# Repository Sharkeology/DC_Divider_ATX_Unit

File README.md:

# DC Divider Project - ATX Base Unit

The ATX Base Unit is part of the larger DC Divider project meant for powering various 12, 9 and 5 volt powered devices (namely games consoles and A/V equipment) from a single ATX power supply unit. The Base Unit was made with the intention of being simple to assemble by beginners and uses off-the-shelf parts and modules.

## Bill of Materials

- 1 x ATX Base Unit PCB
- 1 x Right Angle ATX connector (Molex MiniFit Jr) - PRT-09498
- 3 x MINIVAL-style fuse holders (KEYS3568)
- 1 x LM2596 Adjustable Buck Converter Module
- 3 x Phoenix MSTB-style 2-pin connectors (5.08mm pin spacing)

Once assembled and connected to an ATX supply, the LM2596 module's output voltage can be adjusted to the users needs (although the project was made with 9 volts in mind).

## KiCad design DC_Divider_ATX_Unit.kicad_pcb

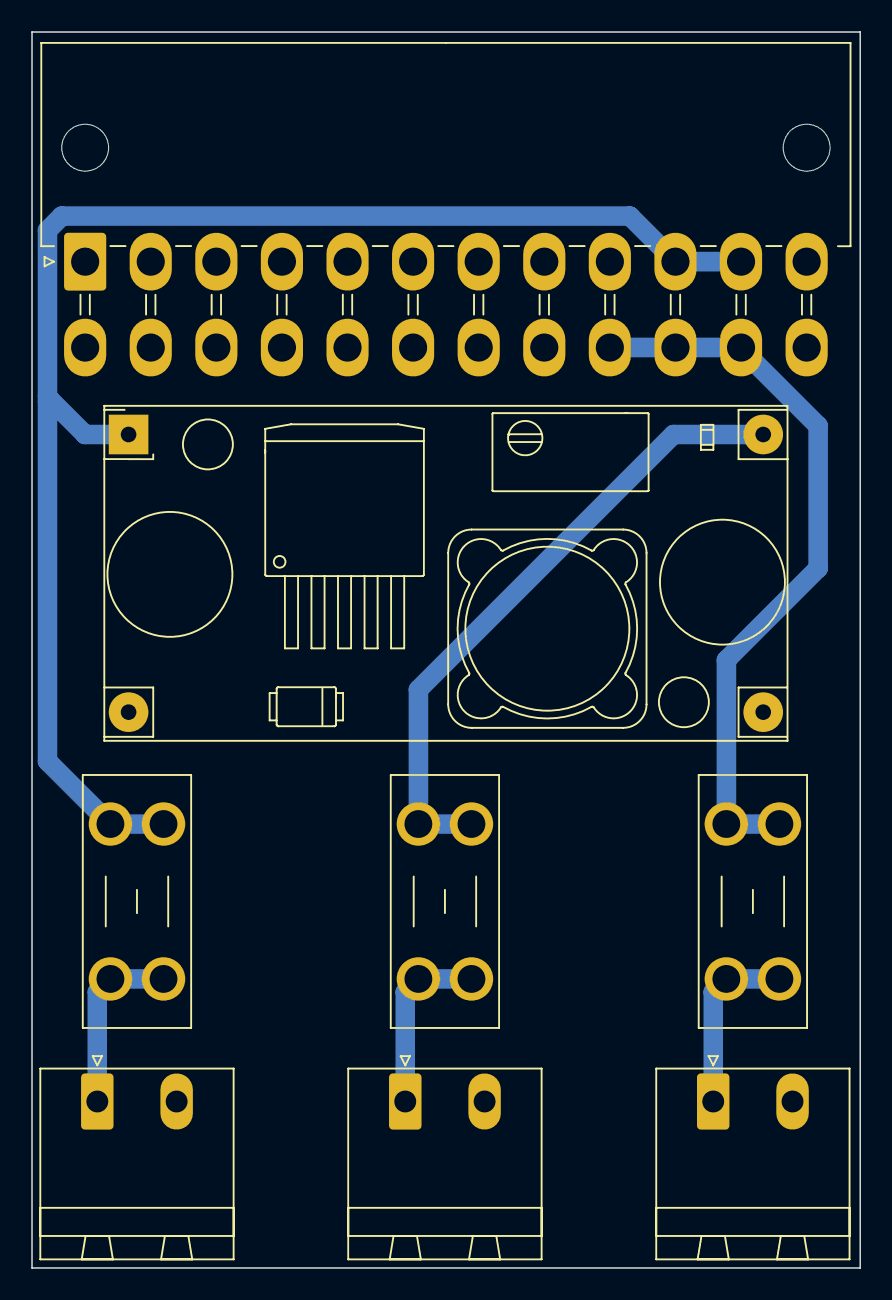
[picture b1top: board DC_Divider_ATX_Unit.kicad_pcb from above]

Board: 2 copper layers, 53.0 x 79.1 mm, 8 parts (0 on the bottom side), 7 nets.

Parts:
F1, F2, F3: Fuse; Fuseholder_Blade_Mini_Keystone_3568
J1: ATX-24; Molex_Mini-Fit_Jr_5569-24A2_2x12_P4.20mm_Horizontal
J2, J3, J4: Conn_01x02; PhoenixContact_MSTBA_2,5_2-G-5,08_1x02_P5.08mm_Horizontal
U1: YAAJ_DCDC_StepDown_LM2596

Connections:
+5V: F3.1, J1.4 (+5V), J1.6 (+5V), J1.21 (+5V), J1.22 (+5V), J1.23 (+5V)
+9V: F2.1, U1.4 (Vout)
+12V: F1.1, J1.10 (+12V), J1.11 (+12V), U1.1 (Vin)
GND: J1.3 (GND), J1.5 (GND), J1.7 (GND), J1.15 (GND), J1.16 (PS_ON#), J1.17 (GND), J1.18 (GND), J1.19 (GND), J1.24 (GND), J2.2, J3.2, J4.2, U1.2 (GND), U1.3 (GND)
unnamed: F1.2, J2.1
unnamed: F2.2, J3.1
unnamed: F3.2, J4.1

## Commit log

2023-06-14 Update README.md
    Included information in README
2023-06-14 Create LICENSE
2023-06-14 Uploaded repo contents.
2023-07-04 Revised PCB design w/ space for fuse holders.
    Minival-like blade fuse holders were included in series with each power rail in order to prevent catastrophic damage to the board in a short circuit/overcurrent situation.
2023-07-04 Update README.md
    Revised BOM and KiCad render.
2023-07-04 Removed gerber_files directory
